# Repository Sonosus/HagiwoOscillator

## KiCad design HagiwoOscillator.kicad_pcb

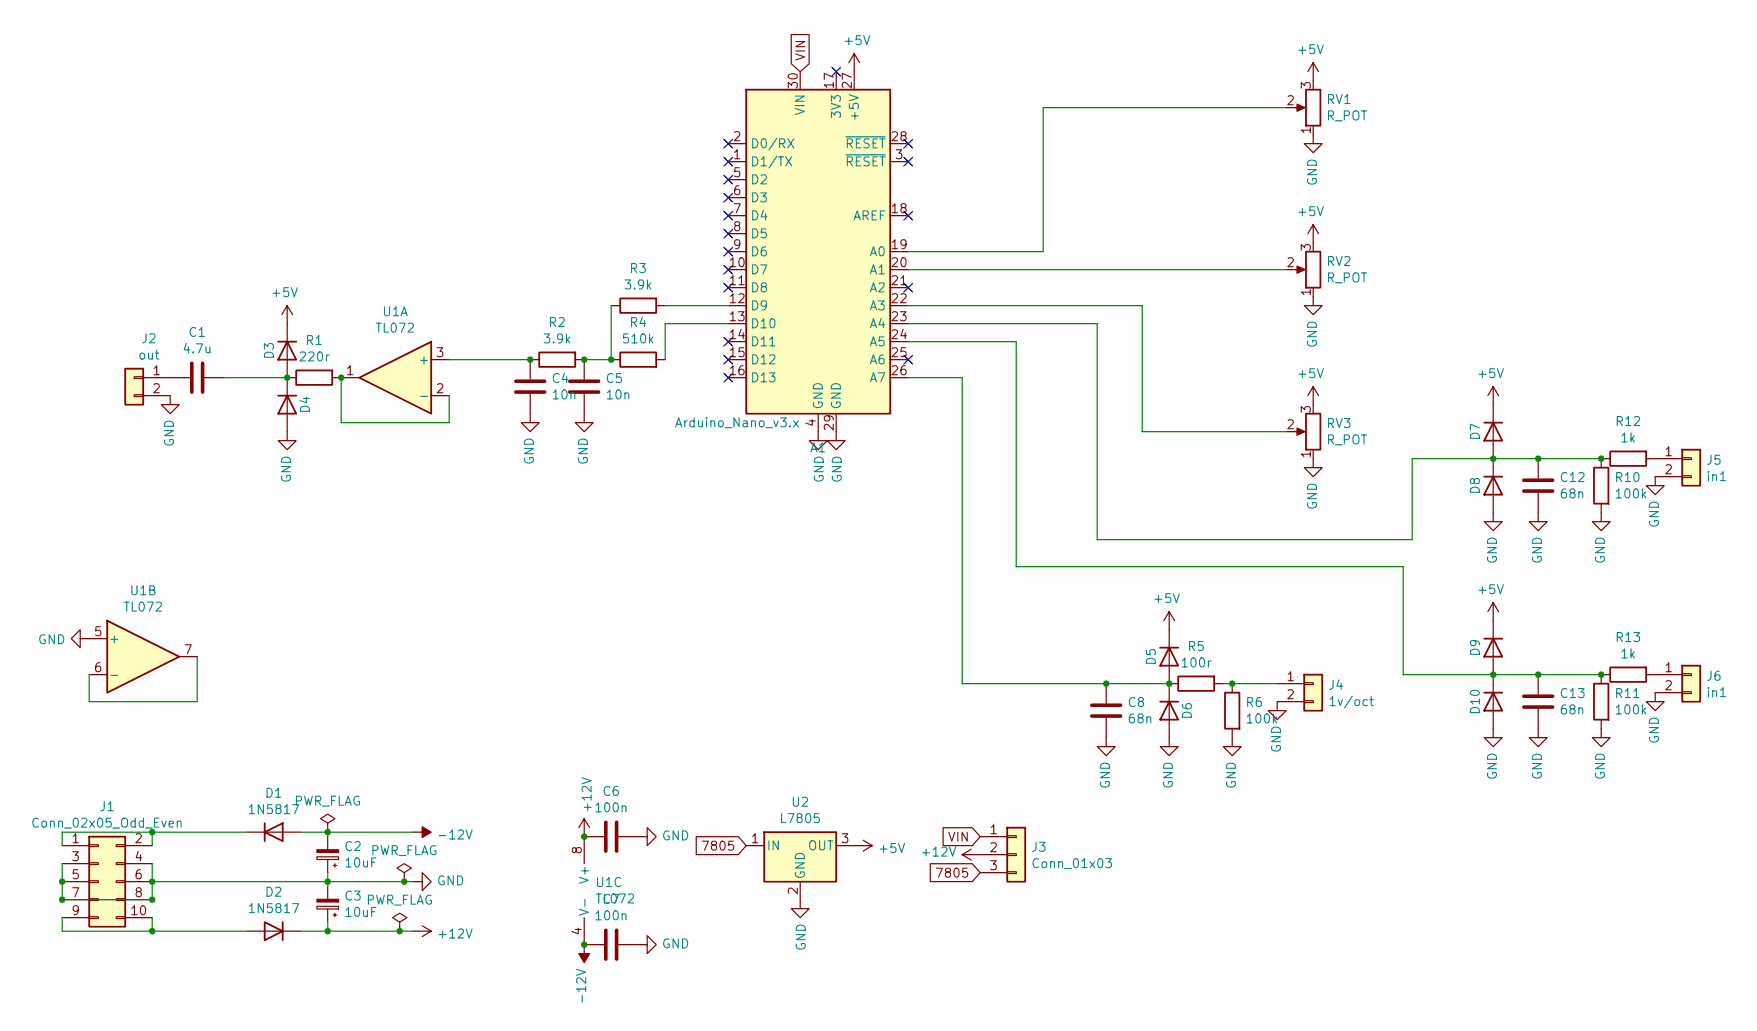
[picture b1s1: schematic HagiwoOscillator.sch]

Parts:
A1: Arduino_Nano_v3.x; Arduino_Nano
C1: 4.7u; Capacitor_NonPolarized
C2, C3: 10uF; Capacitor_Polarized
C4, C5: 10n; Capacitor_NonPolarized
C6, C7: 100n; Capacitor_NonPolarized
C8, C12, C13: 68n; Capacitor_NonPolarized
D1, D2, D3, D4, D5, D6, D7, D8, D9, D10: 1N5817; Diode_DO-35
J1: Conn_02x05_Odd_Even; Power_Header
J2: out; PinHeader_1x02_P2.54mm_Vertical
J3: Conn_01x03; PinHeader_1x03_P2.54mm_Vertical
J4: 1v/oct; PinHeader_1x02_P2.54mm_Vertical
J5, J6: in1; PinHeader_1x02_P2.54mm_Vertical
R1: 220r; Resistor
R2, R3: 3.9k; Resistor
R4: 510k; Resistor
R5: 100r; Resistor
R6, R10, R11: 100k; Resistor
R12, R13: 1k; Resistor
RV1, RV2, RV3: R_POT; Potentiometer_Alpha_RD901F-40-00D_centred
U1: TL072; DIP-8_Socket
U2: L7805; Regulator_TO-220-3

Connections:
7805: J3.3, U2.1 (IN)
+5V: A1.27 (+5V), D3.1 (K), D5.1 (K), D7.1 (K), D9.1 (K), RV1.3, RV2.3, RV3.3, U2.3 (OUT)
+12V: C3.1, C6.2, D2.1 (K), J3.2, U1.8 (V+)
-12V: C2.2, C7.2, D1.2 (A), U1.4 (V-)
GND: A1.4 (GND), A1.29 (GND), C2.1, C3.2, C4.2, C5.2, C6.1, C7.1, C8.2, C12.2, C13.2, D4.2 (A), D6.2 (A), D8.2 (A), D10.2 (A), J1.3, J1.4, J1.5, J1.6, J1.7, J1.8, J2.2, J4.2, J5.2, J6.2, R6.2, R10.2, R11.2, RV1.1, RV2.1, RV3.1, U1.5 (+), U2.2 (GND)
unnamed: A1.12 (D9), R3.2
unnamed: A1.13 (D10), R4.2
unnamed: A1.19 (A0), RV1.2
unnamed: A1.20 (A1), RV2.2
unnamed: A1.22 (A3), RV3.2
unnamed: A1.23 (A4), C12.1, D7.2 (A), D8.1 (K), R10.1, R12.1
unnamed: A1.24 (A5), C13.1, D9.2 (A), D10.1 (K), R11.1, R13.1
unnamed: A1.26 (A7), C8.1, D5.2 (A), D6.1 (K), R5.1
unnamed: C1.1, D3.2 (A), D4.1 (K), R1.1
unnamed: C1.2, J2.1
unnamed: C4.1, R2.1, U1.3 (+)
unnamed: C5.1, R2.2, R3.1, R4.1
unnamed: D1.1 (K), J1.1, J1.2
unnamed: D2.2 (A), J1.9, J1.10
unnamed: J4.1, R5.2, R6.1
unnamed: J5.1, R12.2
unnamed: J6.1, R13.2
unnamed: R1.2, U1.1, U1.2 (-)
unnamed: U1.6 (-), U1.7
VIN: A1.30 (VIN), J3.1

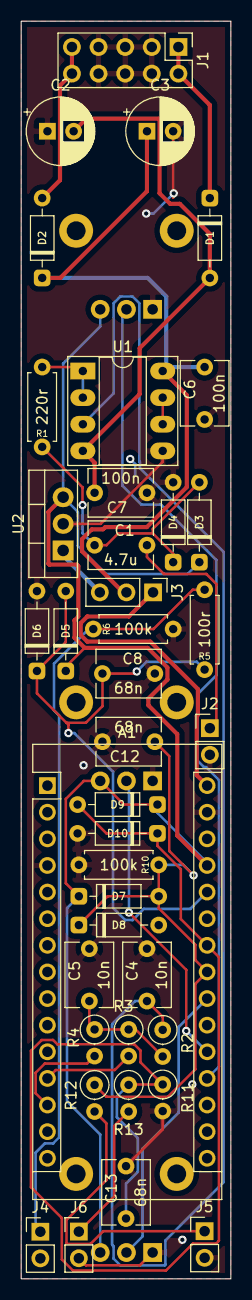
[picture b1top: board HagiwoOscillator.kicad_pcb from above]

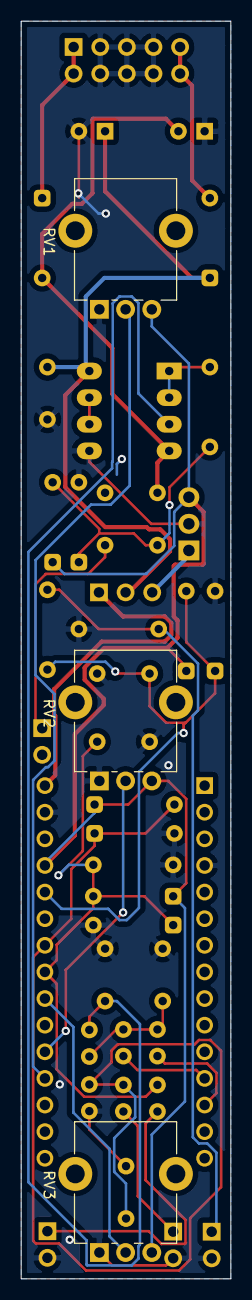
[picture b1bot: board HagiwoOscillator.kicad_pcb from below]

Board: 4 copper layers, 20.0 x 120.0 mm, 42 parts (3 on the bottom side), 25 nets.

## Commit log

2021-07-03 kicad project and add pots
2021-07-03 1voct input
2021-07-03 finish schem
2021-07-03 footprints
2021-07-03 start pcb
2021-08-13 place duino and pots
2021-08-13 remove rs and cs by pots
2021-08-13 update pcb from schem
2021-08-13 place all components
2021-08-14 routed, still many pcb errors
2021-08-14 fix 3dm
